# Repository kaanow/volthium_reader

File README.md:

# Volthium 24V Pack Reader

Reads the state of two Volthium **SC12200G4DPH** 12V 200Ah LiFePO4 batteries
wired in series (24V system, "The Barge Inn"), and shows a live estimate of
time-to-full when charging or time-to-empty (to 10% SOC) when discharging.

> **How it actually runs today (since 2026-07-26).** Nothing runs on the laptop.
> A Raspberry Pi at the cabin reads the packs over **RS485** (BLE is retired)
> and the Conext gear over **Xanbus/CAN**, and ships everything to a cloud
> server at <https://volts.alti2.de>. The laptop is only an operator console.
> The description below is the ORIGINAL laptop-plus-Bluetooth rig and is kept
> for the design reasoning, not as a statement of current fact.
>
> Start here instead: `docs/STATUS.md` for how it runs, `docs/RUNBOOK.md` for
> operating it, and `docs/what-to-distrust.md` before believing any number in
> this repo.

This repo began as the **dev/validation rig** — it ran on a Mac laptop using
its built-in Bluetooth, to check readings against the Volthium phone app and
dial in the time estimator before committing to permanent hardware.

## How it works

The Volthium SC12200G4DPH BLE protocol matches the **E&J Technology BMS**
family — same Nordic UART service, same `:...~` ASCII-hex frames. We use
[`aiobmsble`](https://github.com/patman15/aiobmsble), which already decodes
that protocol, and combine the two single-battery samples into one logical
24V pack reading.

For a series pack:
- pack voltage = `V_a + V_b` (≈ 26V fully charged, ≈ 24V nominal)
- pack current = same through both batteries (we average to suppress noise)
- **charging** finishes when the *higher-SOC* battery hits 100%
- **discharging** finishes when the *lower-SOC* battery hits the floor

The estimator uses an exponential moving average on current so the displayed
"3h 20m" doesn't flicker every time a cloud passes or the inverter steps load.

## Setup

### macOS (dev rig)

```bash
brew install python@3.13        # only if not already installed
/opt/homebrew/bin/python3.13 -m venv .venv
.venv/bin/pip install -r requirements.txt
```

macOS will prompt for Bluetooth permission the first time the Terminal app
tries to scan. Approve it under *System Settings → Privacy & Security → Bluetooth*.

### Linux / Raspberry Pi (cabin-side)

```bash
sudo apt install -y bluez python3-venv rfkill
python3 -m venv .venv
.venv/bin/pip install -r requirements.txt
```

`bluetooth.service` is enabled by the bluez install; bleak talks to it over
D-Bus, no user-group changes needed on Ubuntu 24.04.

The two physical batteries' addresses live in `pack.env` (committed). macOS
sees them under CoreBluetooth peripheral UUIDs; Linux sees the real BLE
MACs. The Mac UUIDs are already filled in; once you've scanned from the Pi:

```bash
.venv/bin/python scripts/scan.py
```

paste the two `V-12V200AH-*` MACs into `pack.env` as `ADDR_A_LINUX` and
`ADDR_B_LINUX` and commit. From then on the launcher just works on either
machine.

## Use

### 1. Find the batteries

```bash
.venv/bin/python scripts/scan.py
```

Both batteries advertise as `V-12V200Ah-<serial>`. Note their BLE addresses.
(Tip: temporarily power one off if you can't tell A from B.)

### 2. Smoke test — one reading

```bash
.venv/bin/python scripts/read_once.py --a AA:BB:CC:DD:EE:FF --b 11:22:33:44:55:66
```

Cross-check the SOC, voltage and current against the Volthium app. If they
match, the protocol is decoded correctly.

### 3. Live dashboard

```bash
.venv/bin/python scripts/monitor.py \
    --a AA:BB:CC:DD:EE:FF \
    --b 11:22:33:44:55:66 \
    --interval 5 \
    --csv pack.csv
```

`--csv` is optional but recommended for the validation phase — we want
real charge/discharge curves to tune the smoothing constant.

### Easiest way to launch (for anyone, no Terminal needed)

**macOS:** Double-click **Volthium Monitor** on the Desktop. It silently
starts the logger + dashboard if they aren't already running, opens the
dashboard in your default browser, and shows a notification with the LAN
URL to share with phones on the same Wi-Fi.

If the Desktop alias gets deleted, recreate it with:

```bash
./scripts/install_desktop_launcher.sh
```

The .app bundle lives at `Volthium Monitor.app/` in the repo root; the
Desktop alias just points at it, so any future improvements to the .app
are picked up automatically.

**Linux / Pi:** Run the same script from a terminal:

```bash
./'Launch Volthium Monitor.command'
```

It's a portable bash script that detects the OS — `caffeinate` is swapped
for `systemd-inhibit`, `ipconfig` for `hostname -I`, `open` for `xdg-open`.
The dashboard binds `0.0.0.0:8421`, so a phone on the same Wi-Fi can hit
the printed LAN URL. `scripts/install_desktop_launcher.sh` also handles
Linux: it writes `~/.local/share/applications/volthium-monitor.desktop`
(plus a Desktop copy if `~/Desktop` exists). On a fully headless Pi,
prefer a systemd unit instead — `Launch Volthium Monitor.command` is the
single command you'd put in the unit's `ExecStart=`.

### 4. Headless logger + browser dashboard

For long unattended runs, the rich-TUI `monitor.py` isn't ideal — it needs a
visible terminal. Use these two together instead:

```bash
# In one terminal — keep alive with `caffeinate -i` so the Mac doesn't doze.
caffeinate -i .venv/bin/python scripts/log.py \
    --a 9058AE7F-F98B-D0F6-237D-6769894DE118 \
    --b 6EC69980-CA43-7DEF-519B-6235C8C535B7 \
    --interval 5 \
    --csv data/pack.csv --log data/pack.log

# In another terminal:
.venv/bin/python scripts/dashboard.py --csv data/pack.csv
# then open http://localhost:8421/
```

The logger never gives up — it backs off and retries on BLE errors. The
dashboard is read-only off the CSV, so both can run forever.

## Files

- `volthium/pack.py` — discovery + `BatteryReading` / `PackReading`
- `volthium/estimator.py` — smoothed time-to-full / time-to-empty
- `scripts/scan.py` — find the batteries
- `scripts/read_once.py` — single-shot smoke test
- `scripts/monitor.py` — live rich-TUI dashboard (one-shot use)
- `scripts/log.py` — headless CSV logger (for unattended runs)
- `scripts/dashboard.py` — browser dashboard (binds LAN by default)
- `scripts/install_desktop_launcher.sh` — re-create the Desktop alias
- `Volthium Monitor.app/` — double-clickable launcher
- `Launch Volthium Monitor.command` — Terminal-friendly launcher with QR code
- **`docs/RUNBOOK.md` — start here for operating the live system**: current deployment, where things live on the Pi, common ops, failure-mode playbook, hardware upgrade path.
- `docs/production_design.md` — architecture for the cabin-side hardware
- `docs/cloud_architecture.md` — Railway telemetry design + repo-wide timestamp convention (ISO-8601 UTC `Z` on the wire; read this before adding any code that emits or consumes timestamps over the network)
- `docs/reliability_failure_modes.md` — field log of BLE / storage failure modes, root causes, and mitigations
- `cloud/` — FastAPI ingest server + Pi-side CSV uploader + browser dashboard, deployable to Railway. See `docs/cloud_architecture.md` § "Railway deploy steps".
- `data/pack.csv`, `data/pack.log` — captured data (gitignored)

## Known limits / open questions

- The Volthium app and our reader **cannot both be connected at once** — the
  BLE peripheral only accepts one central. Close the app before running.
- Capacity defaults to 200 Ah per battery. Override with `--capacity` if the
  batteries have aged.
- The 10% "empty" floor is configurable via `--floor`.
- Range was specified as ~6 m by Volthium; the cabin install will need either
  a closer-range MCU near the batteries or a Bluetooth proxy.

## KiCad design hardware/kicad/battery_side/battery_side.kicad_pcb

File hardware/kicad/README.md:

# `hardware/kicad/` — KiCad design package

Both boards are generated **programmatically** from Python (kiutils +
`kicad-cli`) on **KiCad 10**. The `.kicad_sch` / `.kicad_pcb` files are
build artifacts — edit the generators, not the KiCad files.

## File map

| File / dir      | What                                                          |
|-----------------|---------------------------------------------------------------|
| `schematic/`    | **Schematic source of truth.** `core.py` (shared generator core + full gate stack), `build.py` (battery board), `build_display.py` (display board), `testdata/` (standing poison fixtures for the build-start self-test). Outputs land in `schematic/build/` (battery) and `schematic/build_display/` (display): `.kicad_sch` hierarchy, `.kicad_pro`, netlist, PDF, per-sheet PNGs. |
| `pcb/`          | **Placement/routing source of truth** (CP3+). Same pattern: shared core + per-board build scripts; outputs in `pcb/build/` / `pcb/build_display/`. |
| `libraries/`    | Custom symbols (`volthium.kicad_sym`).                        |
| `footprints/`   | Custom footprints (`volthium.pretty/`) with provenance README. |
| `archive/`      | **Superseded** toolchains: SKiDL/KiCad-8 genesis, plus `pass1_pcb/` (the first design pass's placement/routing generator + board projects + outputs, retired when the design was re-baselined at CP1). See `archive/README.md`. |

## Requirements

- **KiCad 10** with `kicad-cli` discoverable (see the generator's startup
  print for the resolved share/CLI pairing).
- The repo venv (`.venv/`) with kiutils + PyMuPDF.

## Run

```bash
# battery-side schematic (gates + ERC + netlist + PDF/PNG export)
.venv/bin/python hardware/kicad/schematic/build.py
# display-side schematic
.venv/bin/python hardware/kicad/schematic/build_display.py
# battery-side placement (CP3)
.venv/bin/python hardware/kicad/pcb/build.py
```

Every generator carries its own gate stack (readability, glyph, pdf-text
ground truth, netlist intent==actual, exact-part contracts, strict full
ERC/DRC, build-start poison self-tests) and fails the build on any gate.

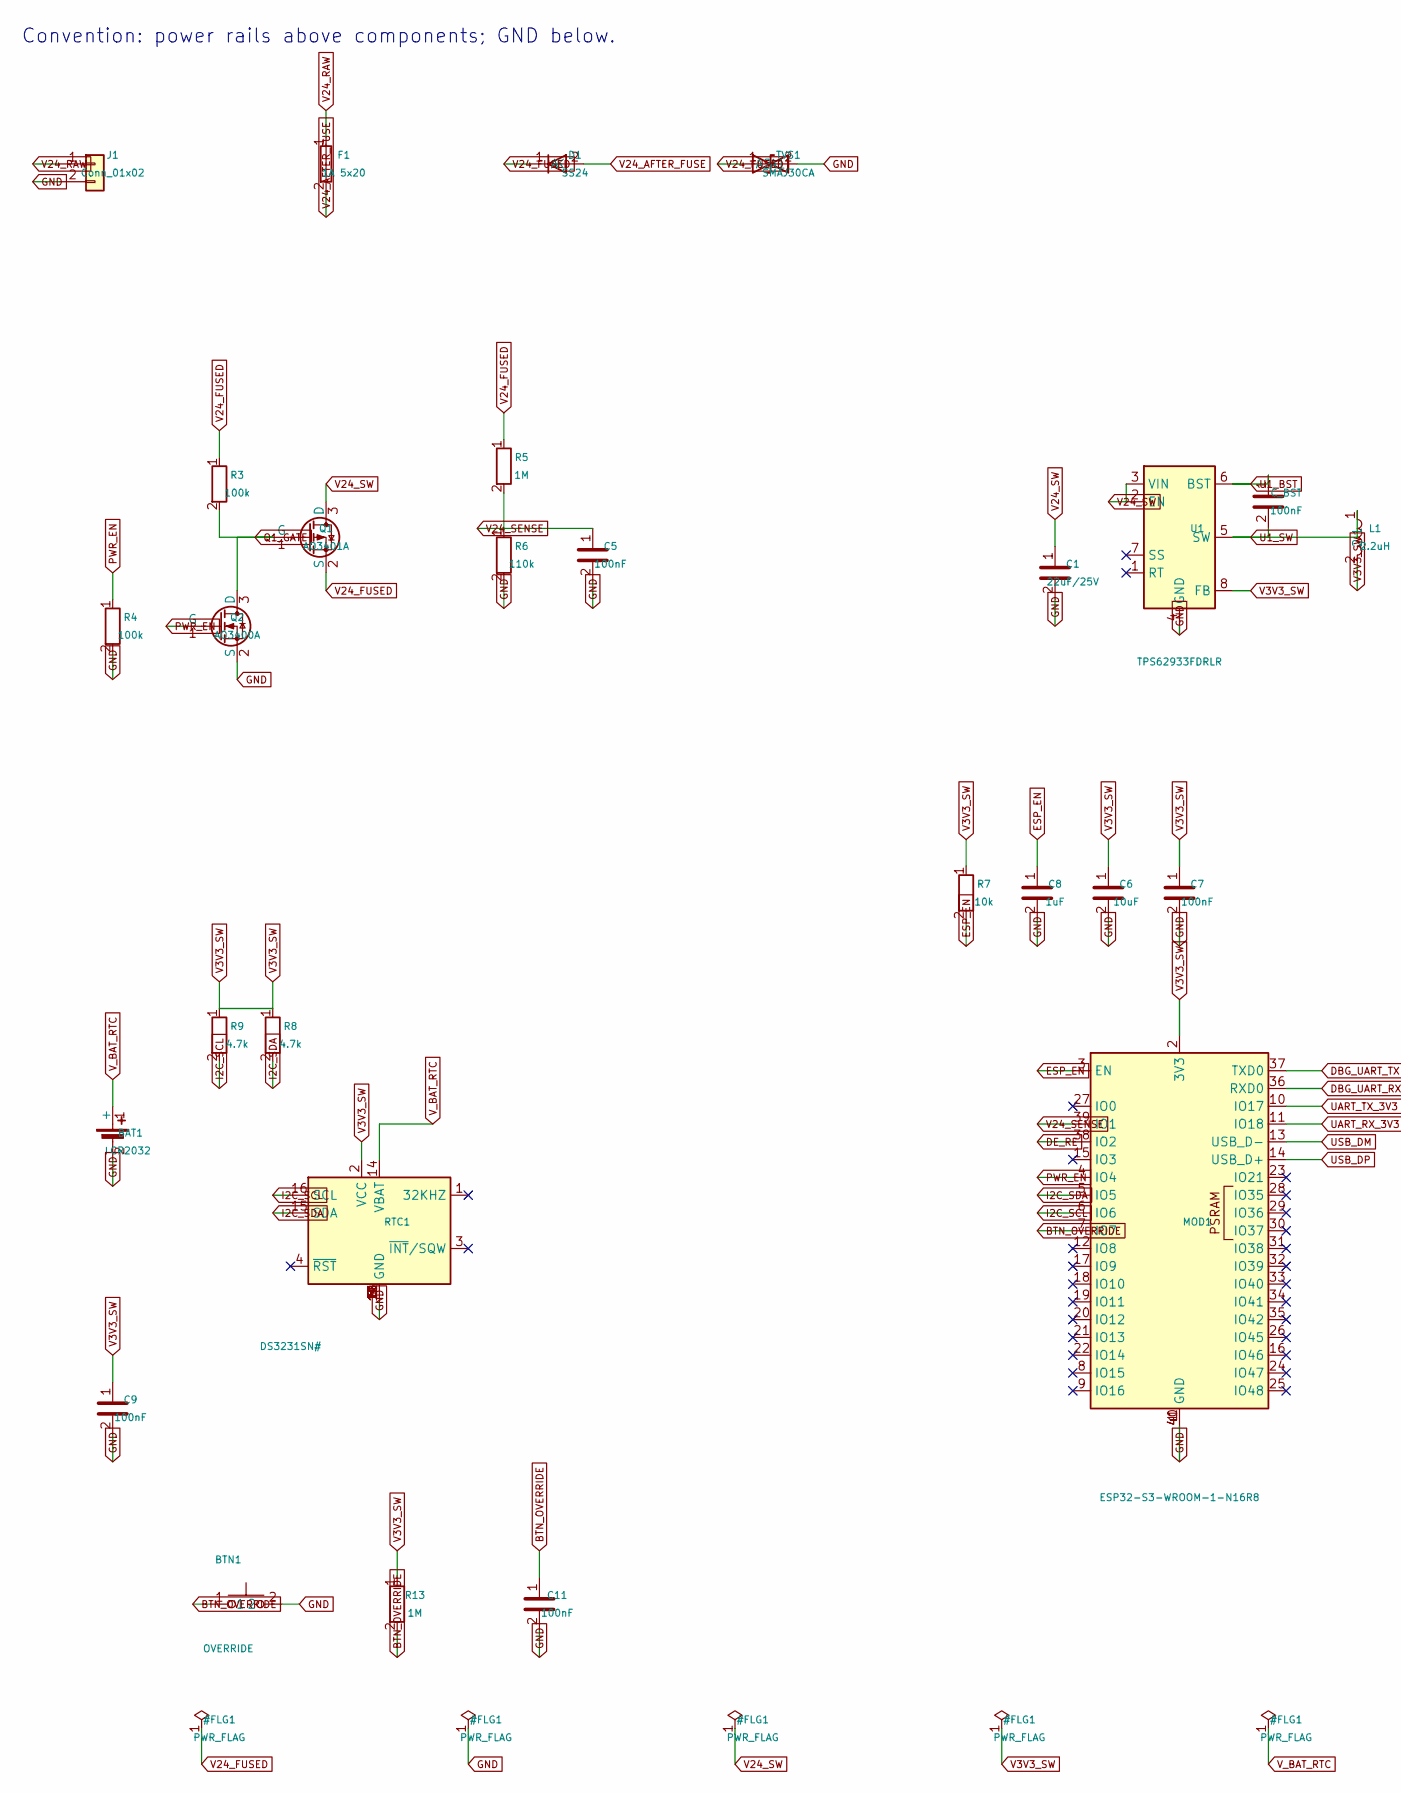
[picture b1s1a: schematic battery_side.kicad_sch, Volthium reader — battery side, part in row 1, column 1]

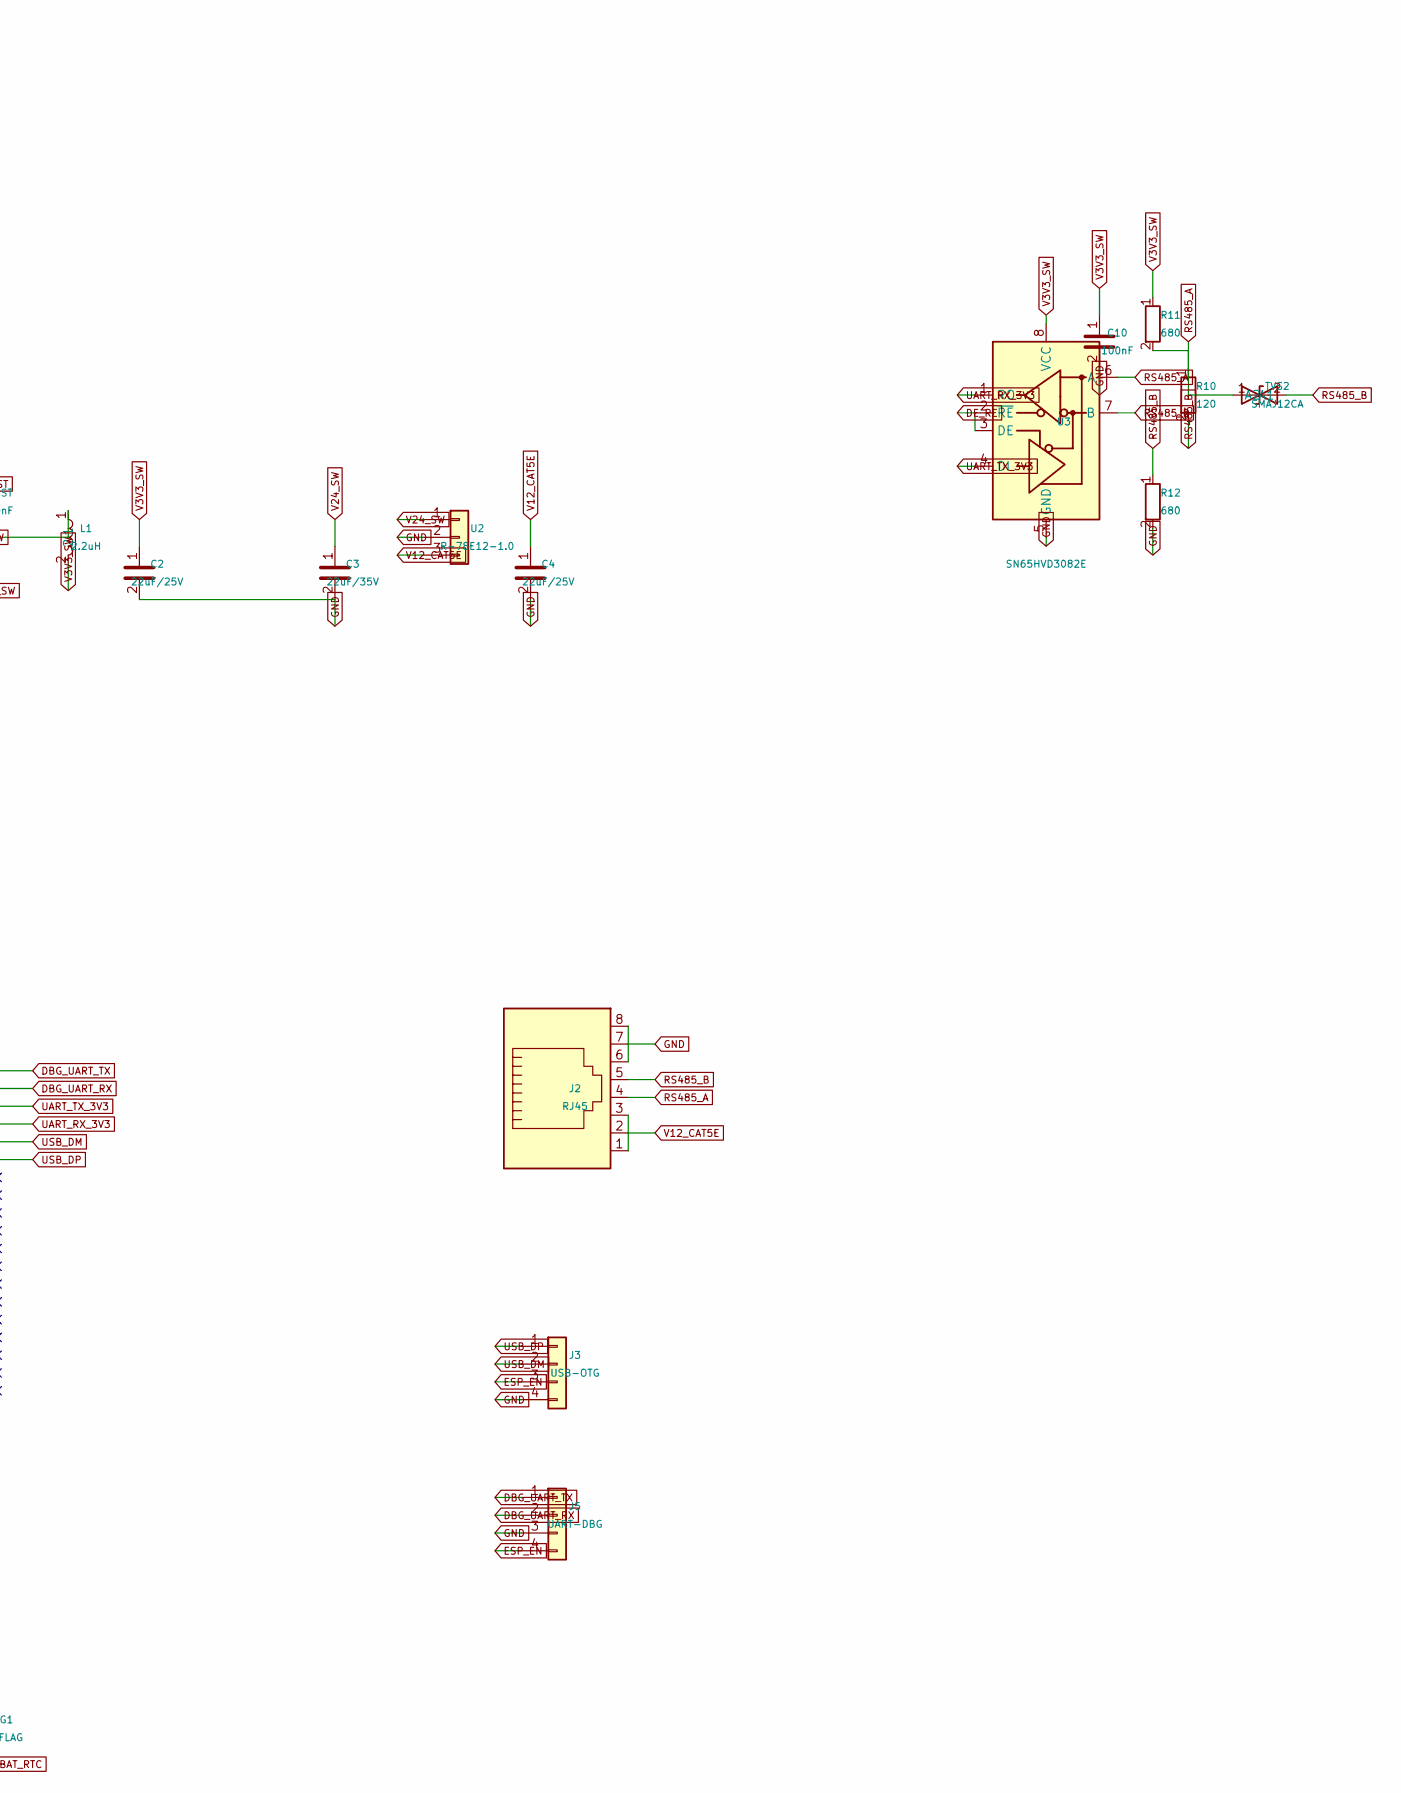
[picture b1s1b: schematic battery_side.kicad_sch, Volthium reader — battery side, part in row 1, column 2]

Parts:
BAT1: CR2032; BatteryHolder_Keystone_1057_1x2032
BTN1: OVERRIDE; SW_PUSH_6mm
C1, C2, C4: 22uF/25V; C_1210_3225Metric
C3: 22uF/35V; C_1210_3225Metric
C5, C9, C10, C11: 100nF; C_0603_1608Metric
C6: 10uF; C_0805_2012Metric
C7: 100nF; C_0402_1005Metric
C8: 1uF; C_0603_1608Metric
C_BST: 100nF; C_0603_1608Metric
D1: SS24; D_SMA
F1: 1A 5x20; Fuseholder_Clip-5x20mm_Bel_FC-203-22_Lateral_P17.80x5.00mm_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
J1: Conn_01x02; TerminalBlock_Phoenix_MKDS-1,5-2-5.08_1x02_P5.08mm_Horizont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
J2: RJ45; RJ45_Amphenol_RJHSE5380
J3: USB-OTG; PinHeader_1x04_P2.54mm_Vertical
J5: UART-DBG; PinHeader_1x04_P2.54mm_Vertical
L1: 2.2uH; L_0805_2012Metric
MOD1: ESP32-S3-WROOM-1-N16R8; ESP32-S3-WROOM-1U
Q1: AO3401A; SOT-23
Q2: AO3400A; SOT-23
R3, R4: 100k; R_0805_2012Metric
R5, R13: 1M; R_0805_2012Metric
R6: 110k; R_0805_2012Metric
R7: 10k; R_0805_2012Metric
R8, R9: 4.7k; R_0805_2012Metric
R10: 120; R_0805_2012Metric
R11, R12: 680; R_0805_2012Metric
RTC1: DS3231SN#; SOIC-16W_7.5x10.3mm_P1.27mm
TVS1: SMAJ30CA; D_SMA
TVS2: SMAJ12CA; D_SMA
U1: TPS62933FDRLR; SOT-23-6
U2: R-78E12-1.0; Converter_DCDC_RECOM_R-78E-0.5_THT
U3: SN65HVD3082E; SOIC-8_3.9x4.9mm_P1.27mm

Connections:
BTN_OVERRIDE: BTN1.1, C11.1, MOD1.7 (IO7), R13.2
DBG_UART_RX: J5.2, MOD1.36 (RXD0)
DBG_UART_TX: J5.1, MOD1.37 (TXD0)
DE_RE: MOD1.38 (IO2), U3.2 (~RE), U3.3 (DE)
ESP_EN: C8.1, J3.3, J5.4, MOD1.3 (EN), R7.2
GND: BAT1.2 (-), BTN1.2, C1.2, C2.2, C3.2, C4.2, C5.2, C6.2, C7.2, C8.2, C9.2, C10.2, C11.2, J1.2, J2.6, J2.7, J2.8, J3.4, J5.3, MOD1.1 (GND), MOD1.40 (GND), MOD1.41 (GND), Q2.2 (S), R4.2, R6.2, R12.2, RTC1.5 (GND), RTC1.6 (GND), RTC1.7 (GND), RTC1.8 (GND), RTC1.9 (GND), RTC1.10 (GND), RTC1.11 (GND), RTC1.12 (GND), RTC1.13 (GND), TVS1.2 (A2), U1.4 (GND), U2.2, U3.5 (GND)
I2C_SCL: MOD1.6 (IO6), R9.2, RTC1.16 (SCL)
I2C_SDA: MOD1.5 (IO5), R8.2, RTC1.15 (SDA)
PWR_EN: MOD1.4 (IO4), Q2.1 (G), R4.1
Q1_GATE: Q1.1 (G), Q2.3 (D), R3.2
RS485_A: J2.4, R10.1, R11.2, TVS2.1 (A1), U3.6 (A)
RS485_B: J2.5, R10.2, R12.1, TVS2.2 (A2), U3.7 (B)
U1_BST: C_BST.1, U1.6 (BST)
U1_SW: C_BST.2, L1.1, U1.5 (SW)
UART_RX_3V3: MOD1.11 (IO18), U3.1 (RO)
UART_TX_3V3: MOD1.10 (IO17), U3.4 (DI)
USB_DM: J3.2, MOD1.13 (USB_D-)
USB_DP: J3.1, MOD1.14 (USB_D+)
V3V3_SW: C2.1, C6.1, C7.1, C9.1, C10.1, L1.2, MOD1.2 (3V3), R7.1, R8.1, R9.1, R11.1, R13.1, RTC1.2 (VCC), U1.8 (FB), U3.8 (VCC)
V12_CAT5E: C4.1, J2.1, J2.2, J2.3, U2.3
V24_AFTER_FUSE: D1.2 (A), F1.2
V24_FUSED: D1.1 (K), Q1.2 (S), R3.1, R5.1, TVS1.1 (A1)
V24_RAW: F1.1, J1.1
V24_SENSE: C5.1, MOD1.39 (IO1), R5.2, R6.1
V24_SW: C1.1, C3.1, Q1.3 (D), U1.2 (EN), U1.3 (VIN), U2.1
V_BAT_RTC: BAT1.1 (+), RTC1.14 (VBAT)

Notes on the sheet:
Convention: power rails above components; GND below.

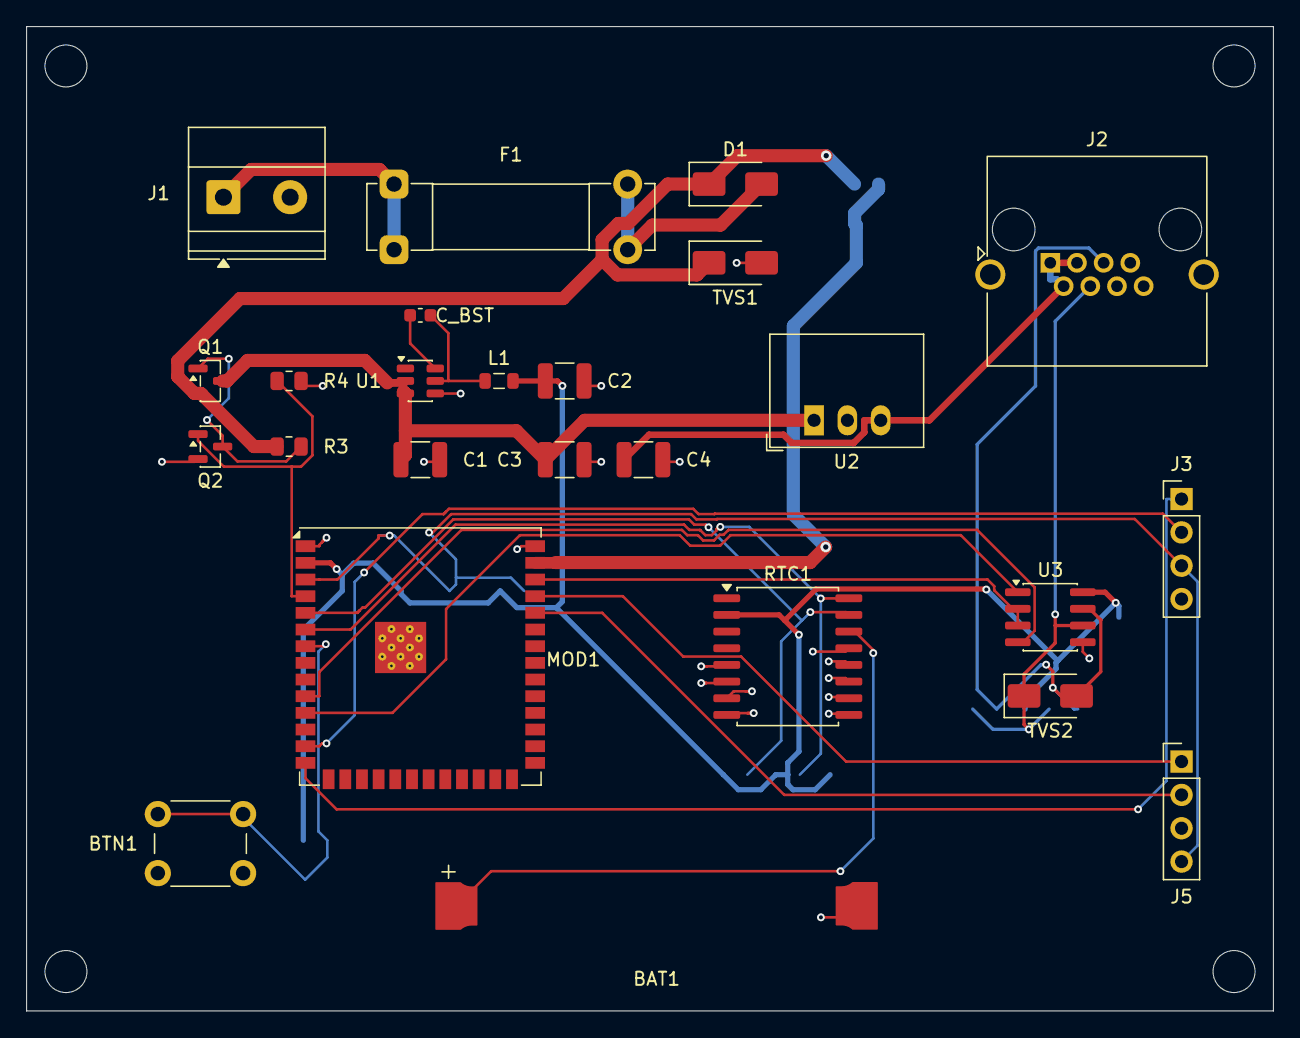
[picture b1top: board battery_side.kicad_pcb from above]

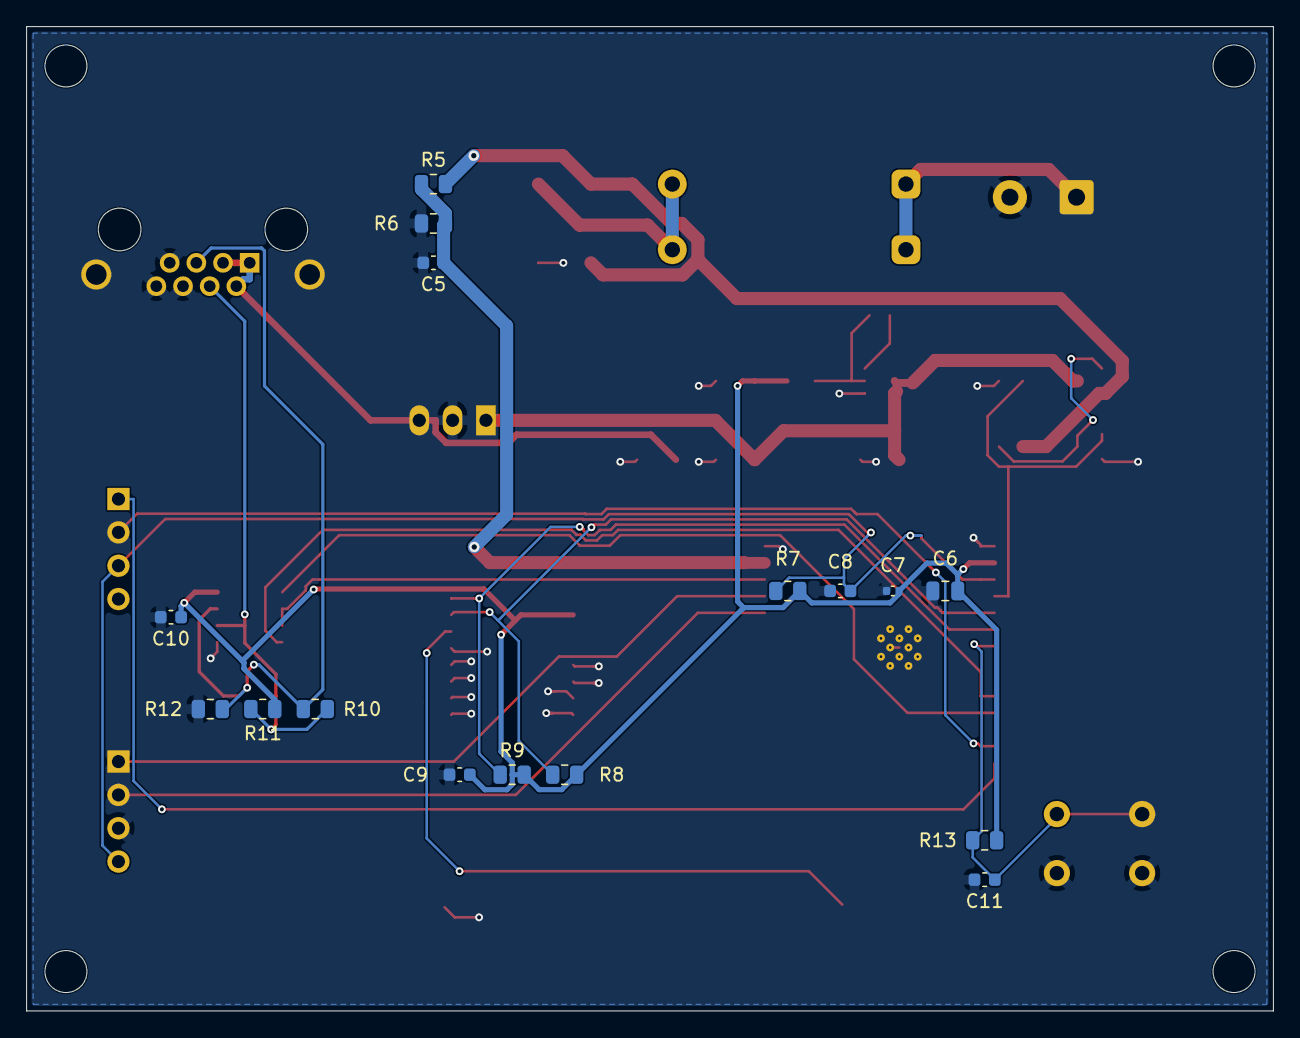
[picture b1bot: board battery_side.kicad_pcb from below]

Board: 2 copper layers, 95.0 x 75.0 mm, 45 parts (16 on the bottom side), 26 nets.

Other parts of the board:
H1, H2, H3, H4: MountingHole_3.2mm; MountingHole_3.2mm_M3_DIN965

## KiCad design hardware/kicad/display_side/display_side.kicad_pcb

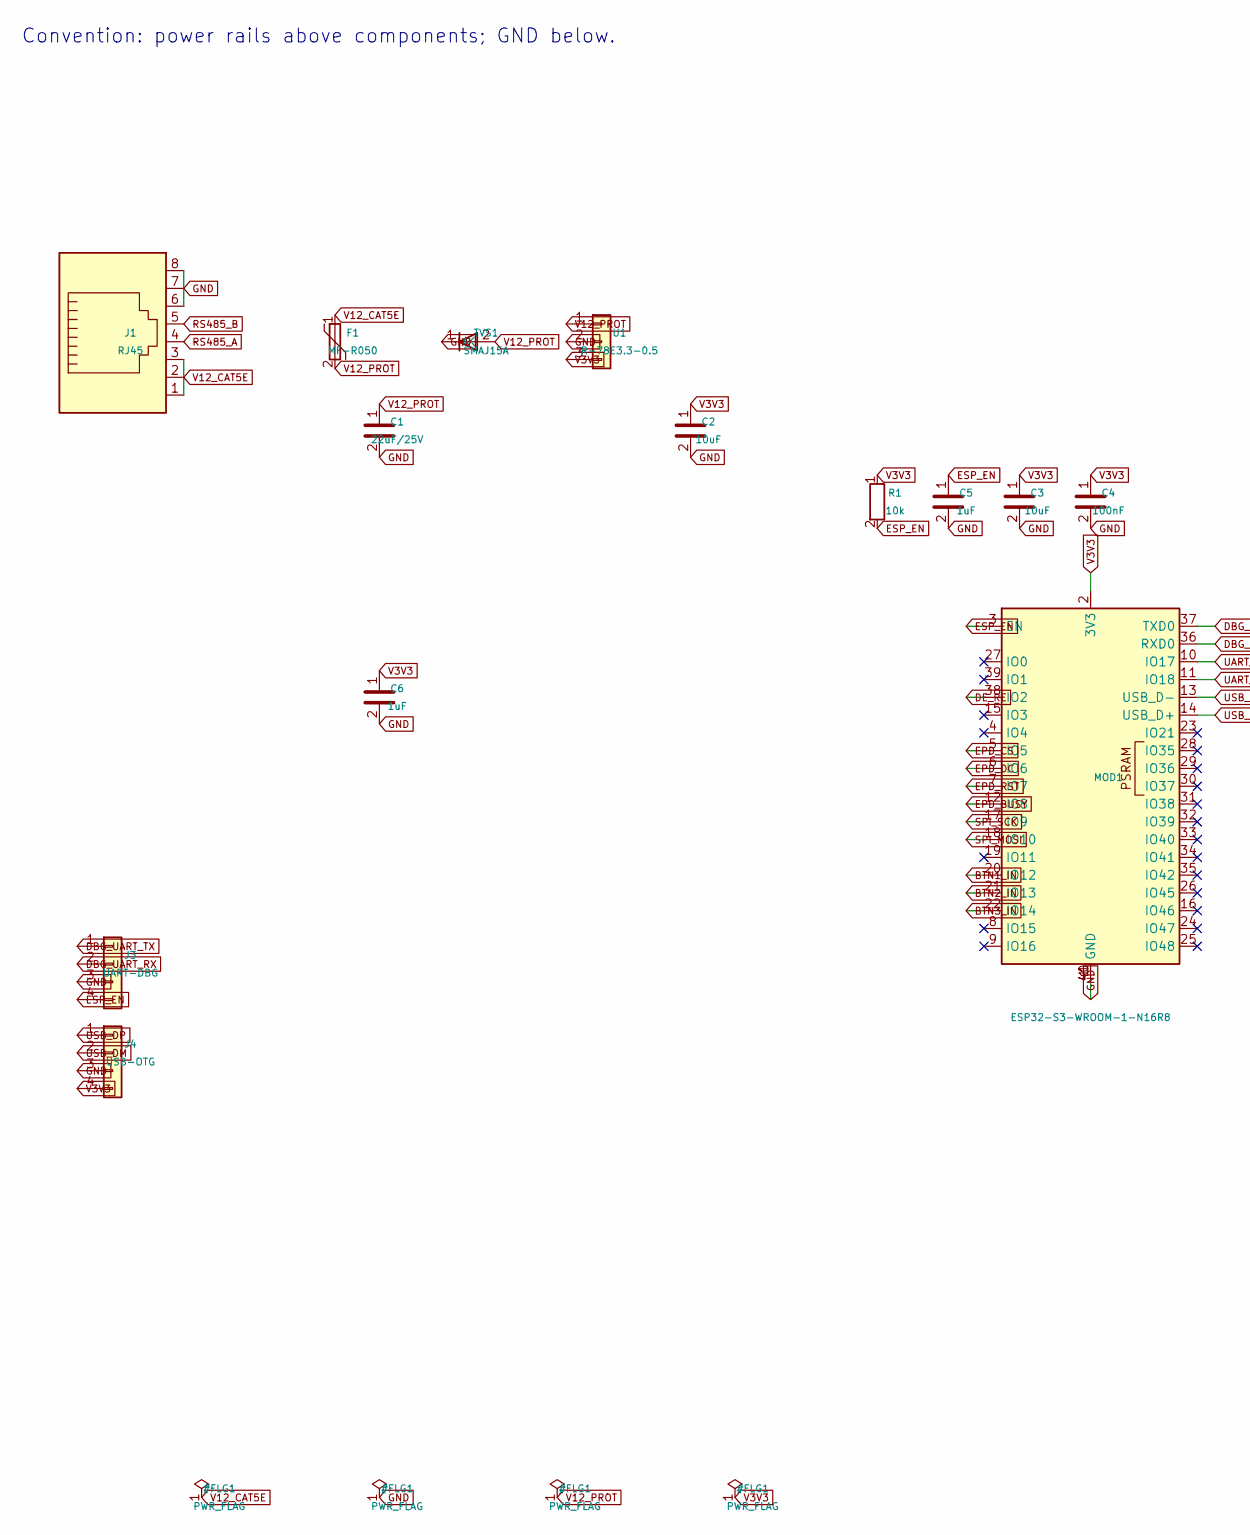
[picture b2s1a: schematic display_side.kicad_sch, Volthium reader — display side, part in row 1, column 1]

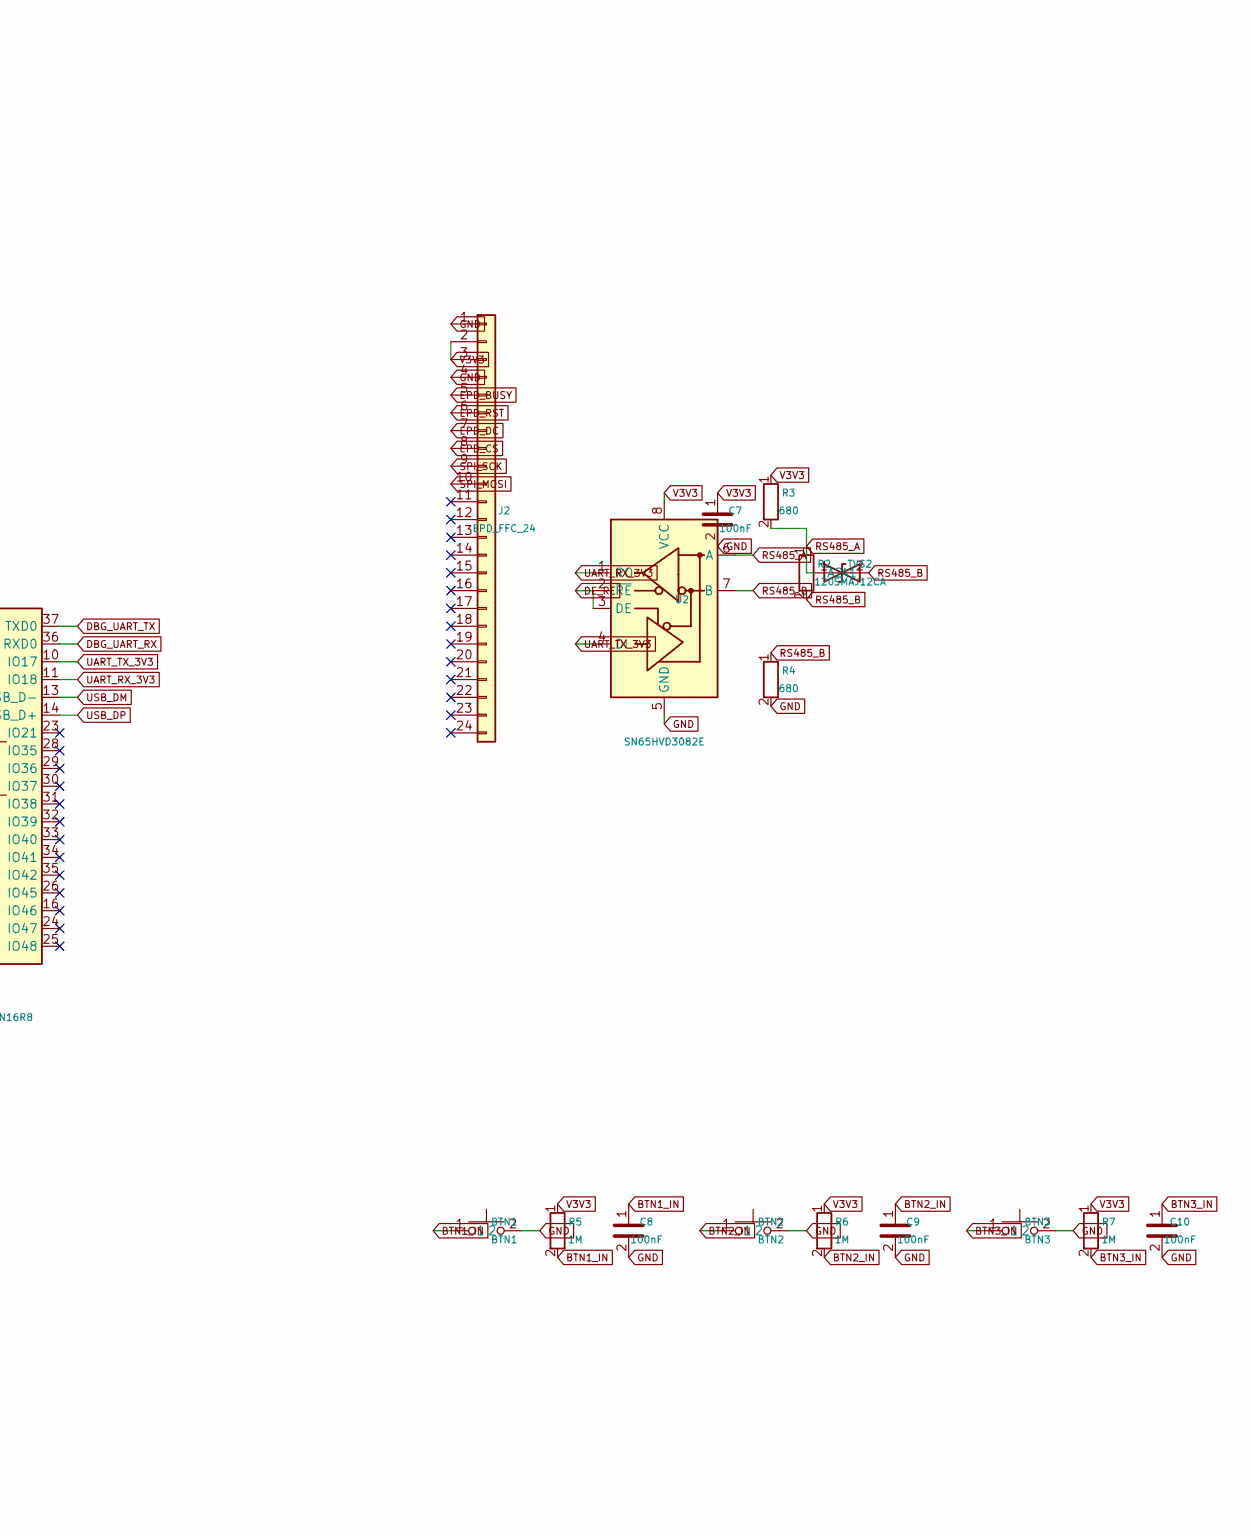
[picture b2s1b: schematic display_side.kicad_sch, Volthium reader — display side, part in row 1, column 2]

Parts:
BTN1: BTN1; SW_SPST_B3S-1000
BTN2: BTN2; SW_SPST_B3S-1000
BTN3: BTN3; SW_SPST_B3S-1000
C1: 22uF/25V; C_1210_3225Metric
C2, C3: 10uF; C_0805_2012Metric
C4: 100nF; C_0402_1005Metric
C5, C6: 1uF; C_0603_1608Metric
C7, C8, C9, C10: 100nF; C_0603_1608Metric
F1: MF-R050; R_Axial_DIN0207_L6.3mm_D2.5mm_P10.16mm_Horizontal
J1: RJ45; RJ45_Amphenol_RJHSE5380
J2: EPD_FFC_24; Hirose_FH12-24S-0.5SH_1x24-1MP_P0.50mm_Horizontal
J3: UART-DBG; PinHeader_1x04_P2.54mm_Vertical
J4: USB-OTG; PinHeader_1x04_P2.54mm_Vertical
MOD1: ESP32-S3-WROOM-1-N16R8; ESP32-S3-WROOM-1U
R1: 10k; R_0805_2012Metric
R2: 120; R_0805_2012Metric
R3, R4: 680; R_0805_2012Metric
R5, R6, R7: 1M; R_0805_2012Metric
TVS1: SMAJ15A; D_SMA
TVS2: SMAJ12CA; D_SMA
U1: R-78E3.3-0.5; Converter_DCDC_RECOM_R-78E-0.5_THT
U2: SN65HVD3082E; SOIC-8_3.9x4.9mm_P1.27mm

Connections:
BTN1_IN: BTN1.1, C8.1, MOD1.20 (IO12), R5.2
BTN2_IN: BTN2.1, C9.1, MOD1.21 (IO13), R6.2
BTN3_IN: BTN3.1, C10.1, MOD1.22 (IO14), R7.2
DBG_UART_RX: J3.2, MOD1.36 (RXD0)
DBG_UART_TX: J3.1, MOD1.37 (TXD0)
DE_RE: MOD1.38 (IO2), U2.2 (~RE), U2.3 (DE)
EPD_BUSY: J2.5, MOD1.12 (IO8)
EPD_CS: J2.8, MOD1.5 (IO5)
EPD_DC: J2.7, MOD1.6 (IO6)
EPD_RST: J2.6, MOD1.7 (IO7)
ESP_EN: C5.1, J3.4, MOD1.3 (EN), R1.2
GND: BTN1.2, BTN2.2, BTN3.2, C1.2, C2.2, C3.2, C4.2, C5.2, C6.2, C7.2, C8.2, C9.2, C10.2, J1.6, J1.7, J1.8, J2.1, J2.4, J3.3, J4.3, MOD1.1 (GND), MOD1.40 (GND), MOD1.41 (GND), R4.2, TVS1.1 (K), U1.2, U2.5 (GND)
RS485_A: J1.4, R2.1, R3.2, TVS2.1 (A1), U2.6 (A)
RS485_B: J1.5, R2.2, R4.1, TVS2.2 (A2), U2.7 (B)
SPI_MOSI: J2.10, MOD1.18 (IO10)
SPI_SCK: J2.9, MOD1.17 (IO9)
UART_RX_3V3: MOD1.11 (IO18), U2.1 (RO)
UART_TX_3V3: MOD1.10 (IO17), U2.4 (DI)
USB_DM: J4.2, MOD1.13 (USB_D-)
USB_DP: J4.1, MOD1.14 (USB_D+)
V3V3: C2.1, C3.1, C4.1, C6.1, C7.1, J2.2, J2.3, J4.4, MOD1.2 (3V3), R1.1, R3.1, R5.1, R6.1, R7.1, U1.3, U2.8 (VCC)
V12_CAT5E: F1.1, J1.1, J1.2, J1.3
V12_PROT: C1.1, F1.2, TVS1.2 (A), U1.1

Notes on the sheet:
Convention: power rails above components; GND below.

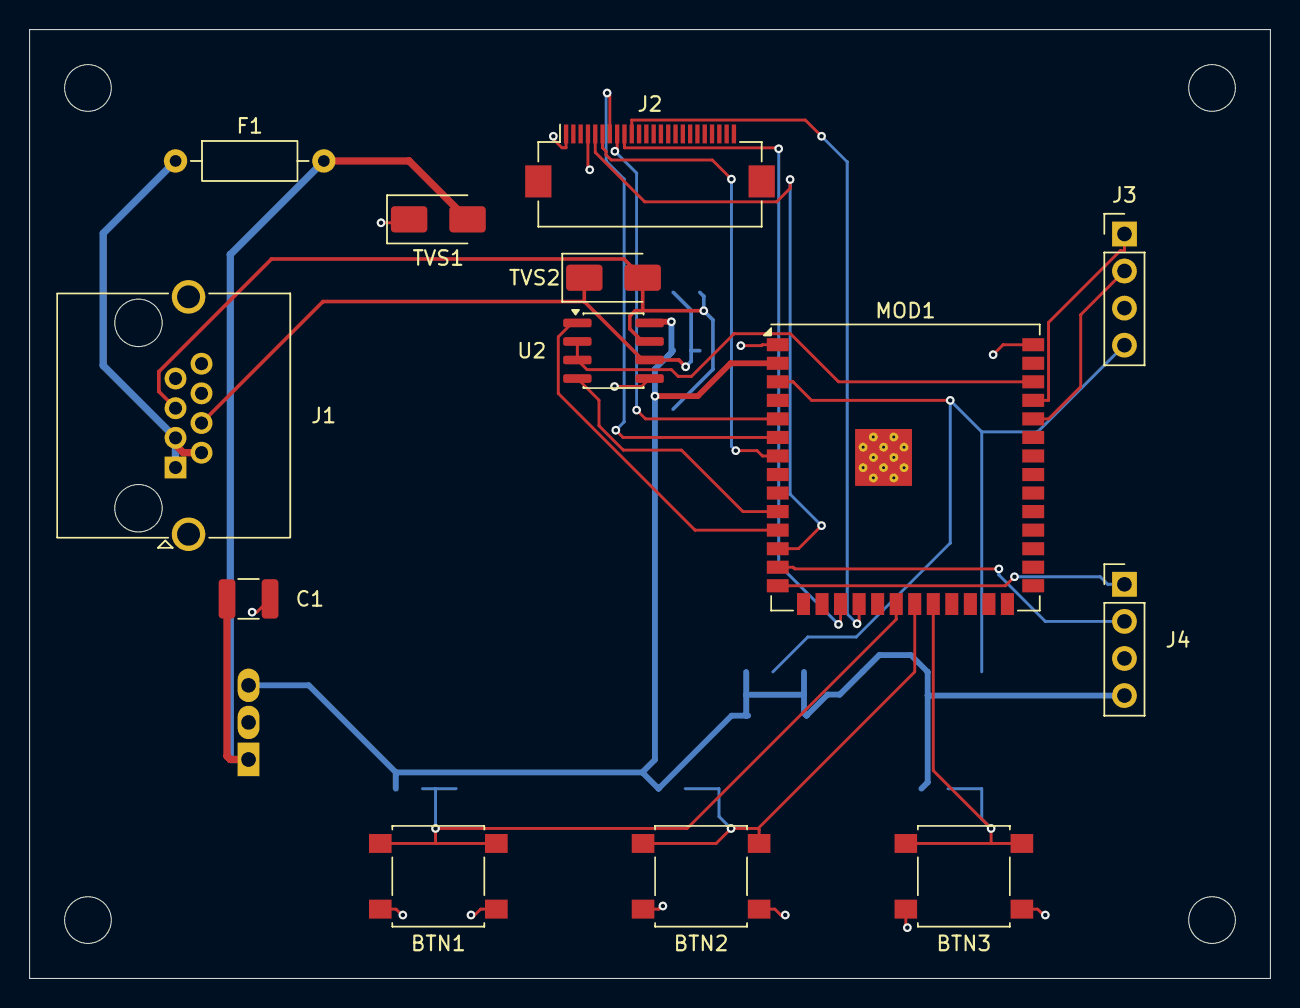
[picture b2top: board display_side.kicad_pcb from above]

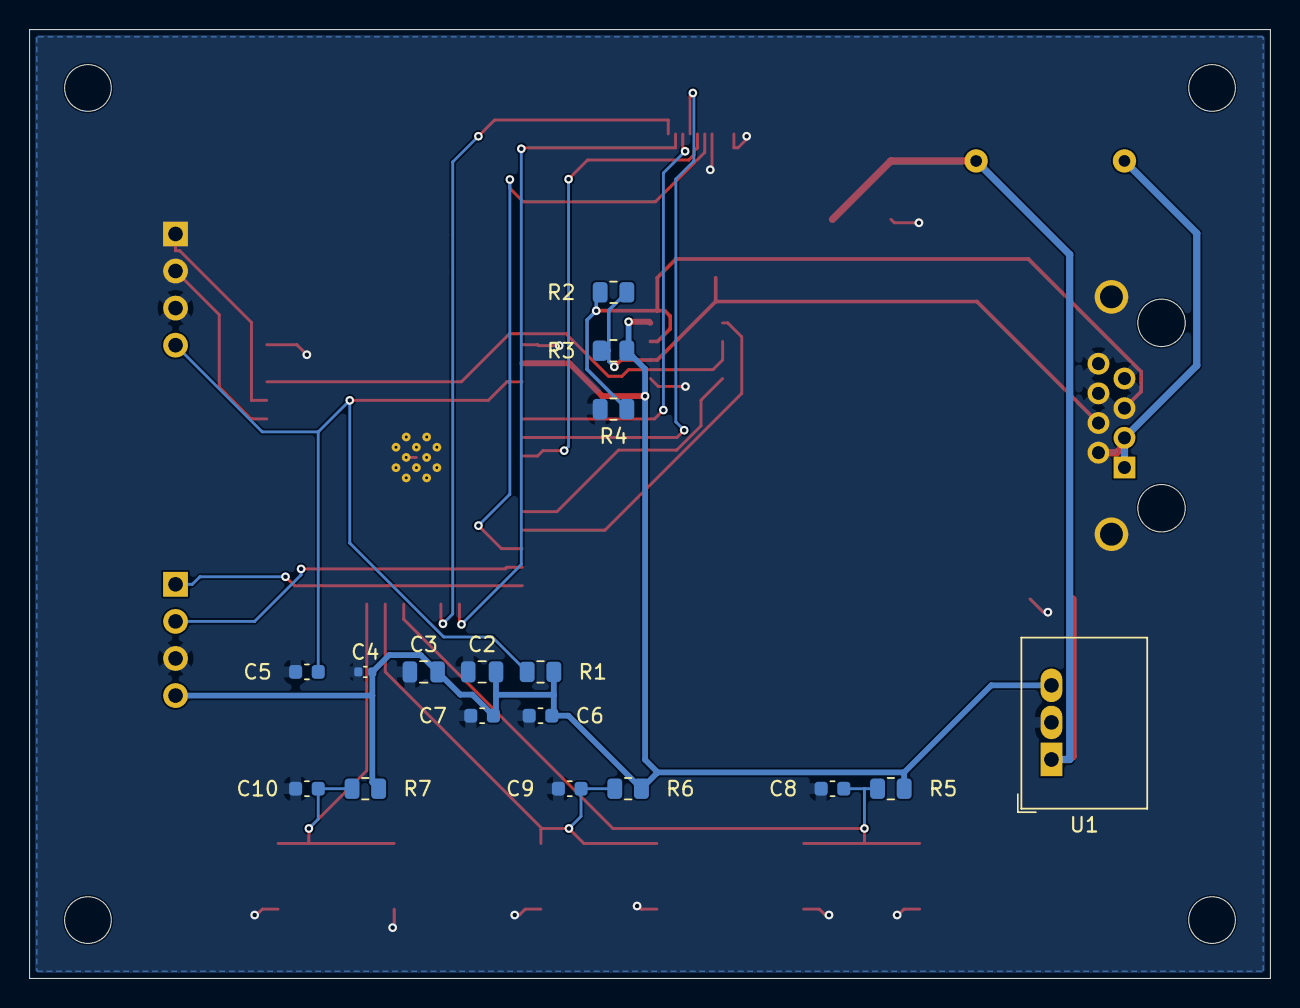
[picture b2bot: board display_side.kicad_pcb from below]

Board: 2 copper layers, 85.0 x 65.0 mm, 34 parts (17 on the bottom side), 23 nets.

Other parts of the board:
H1, H2, H3, H4: MountingHole_3.2mm; MountingHole_3.2mm_M3_DIN965
